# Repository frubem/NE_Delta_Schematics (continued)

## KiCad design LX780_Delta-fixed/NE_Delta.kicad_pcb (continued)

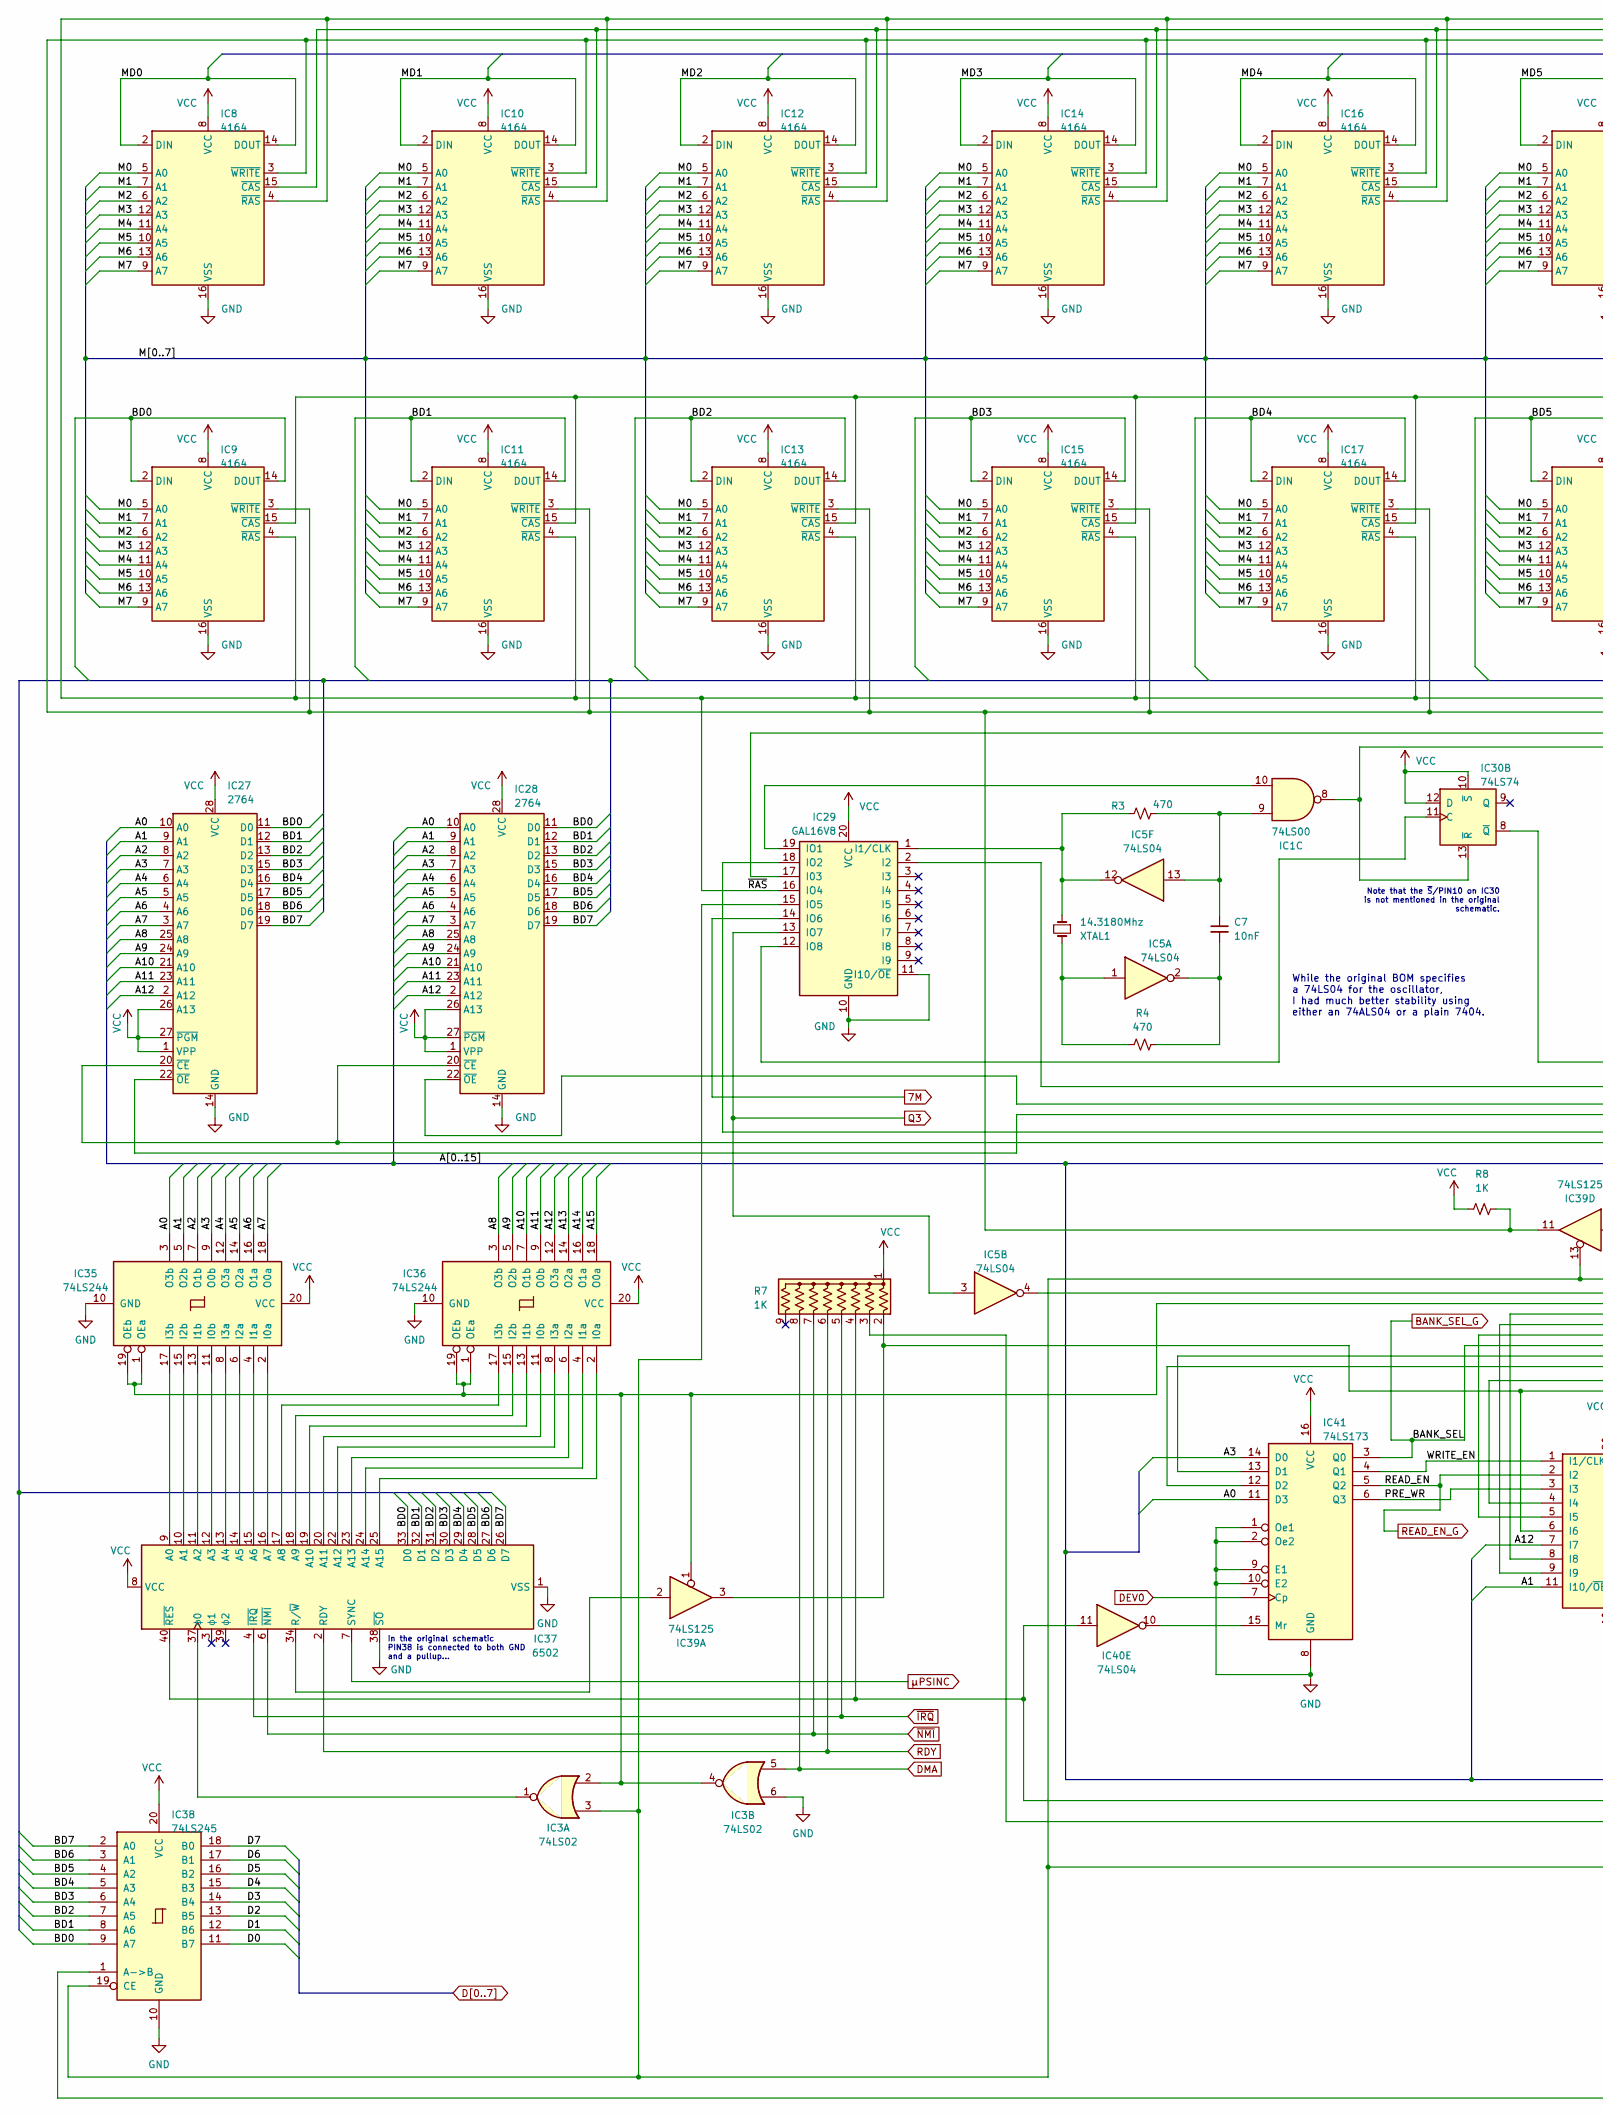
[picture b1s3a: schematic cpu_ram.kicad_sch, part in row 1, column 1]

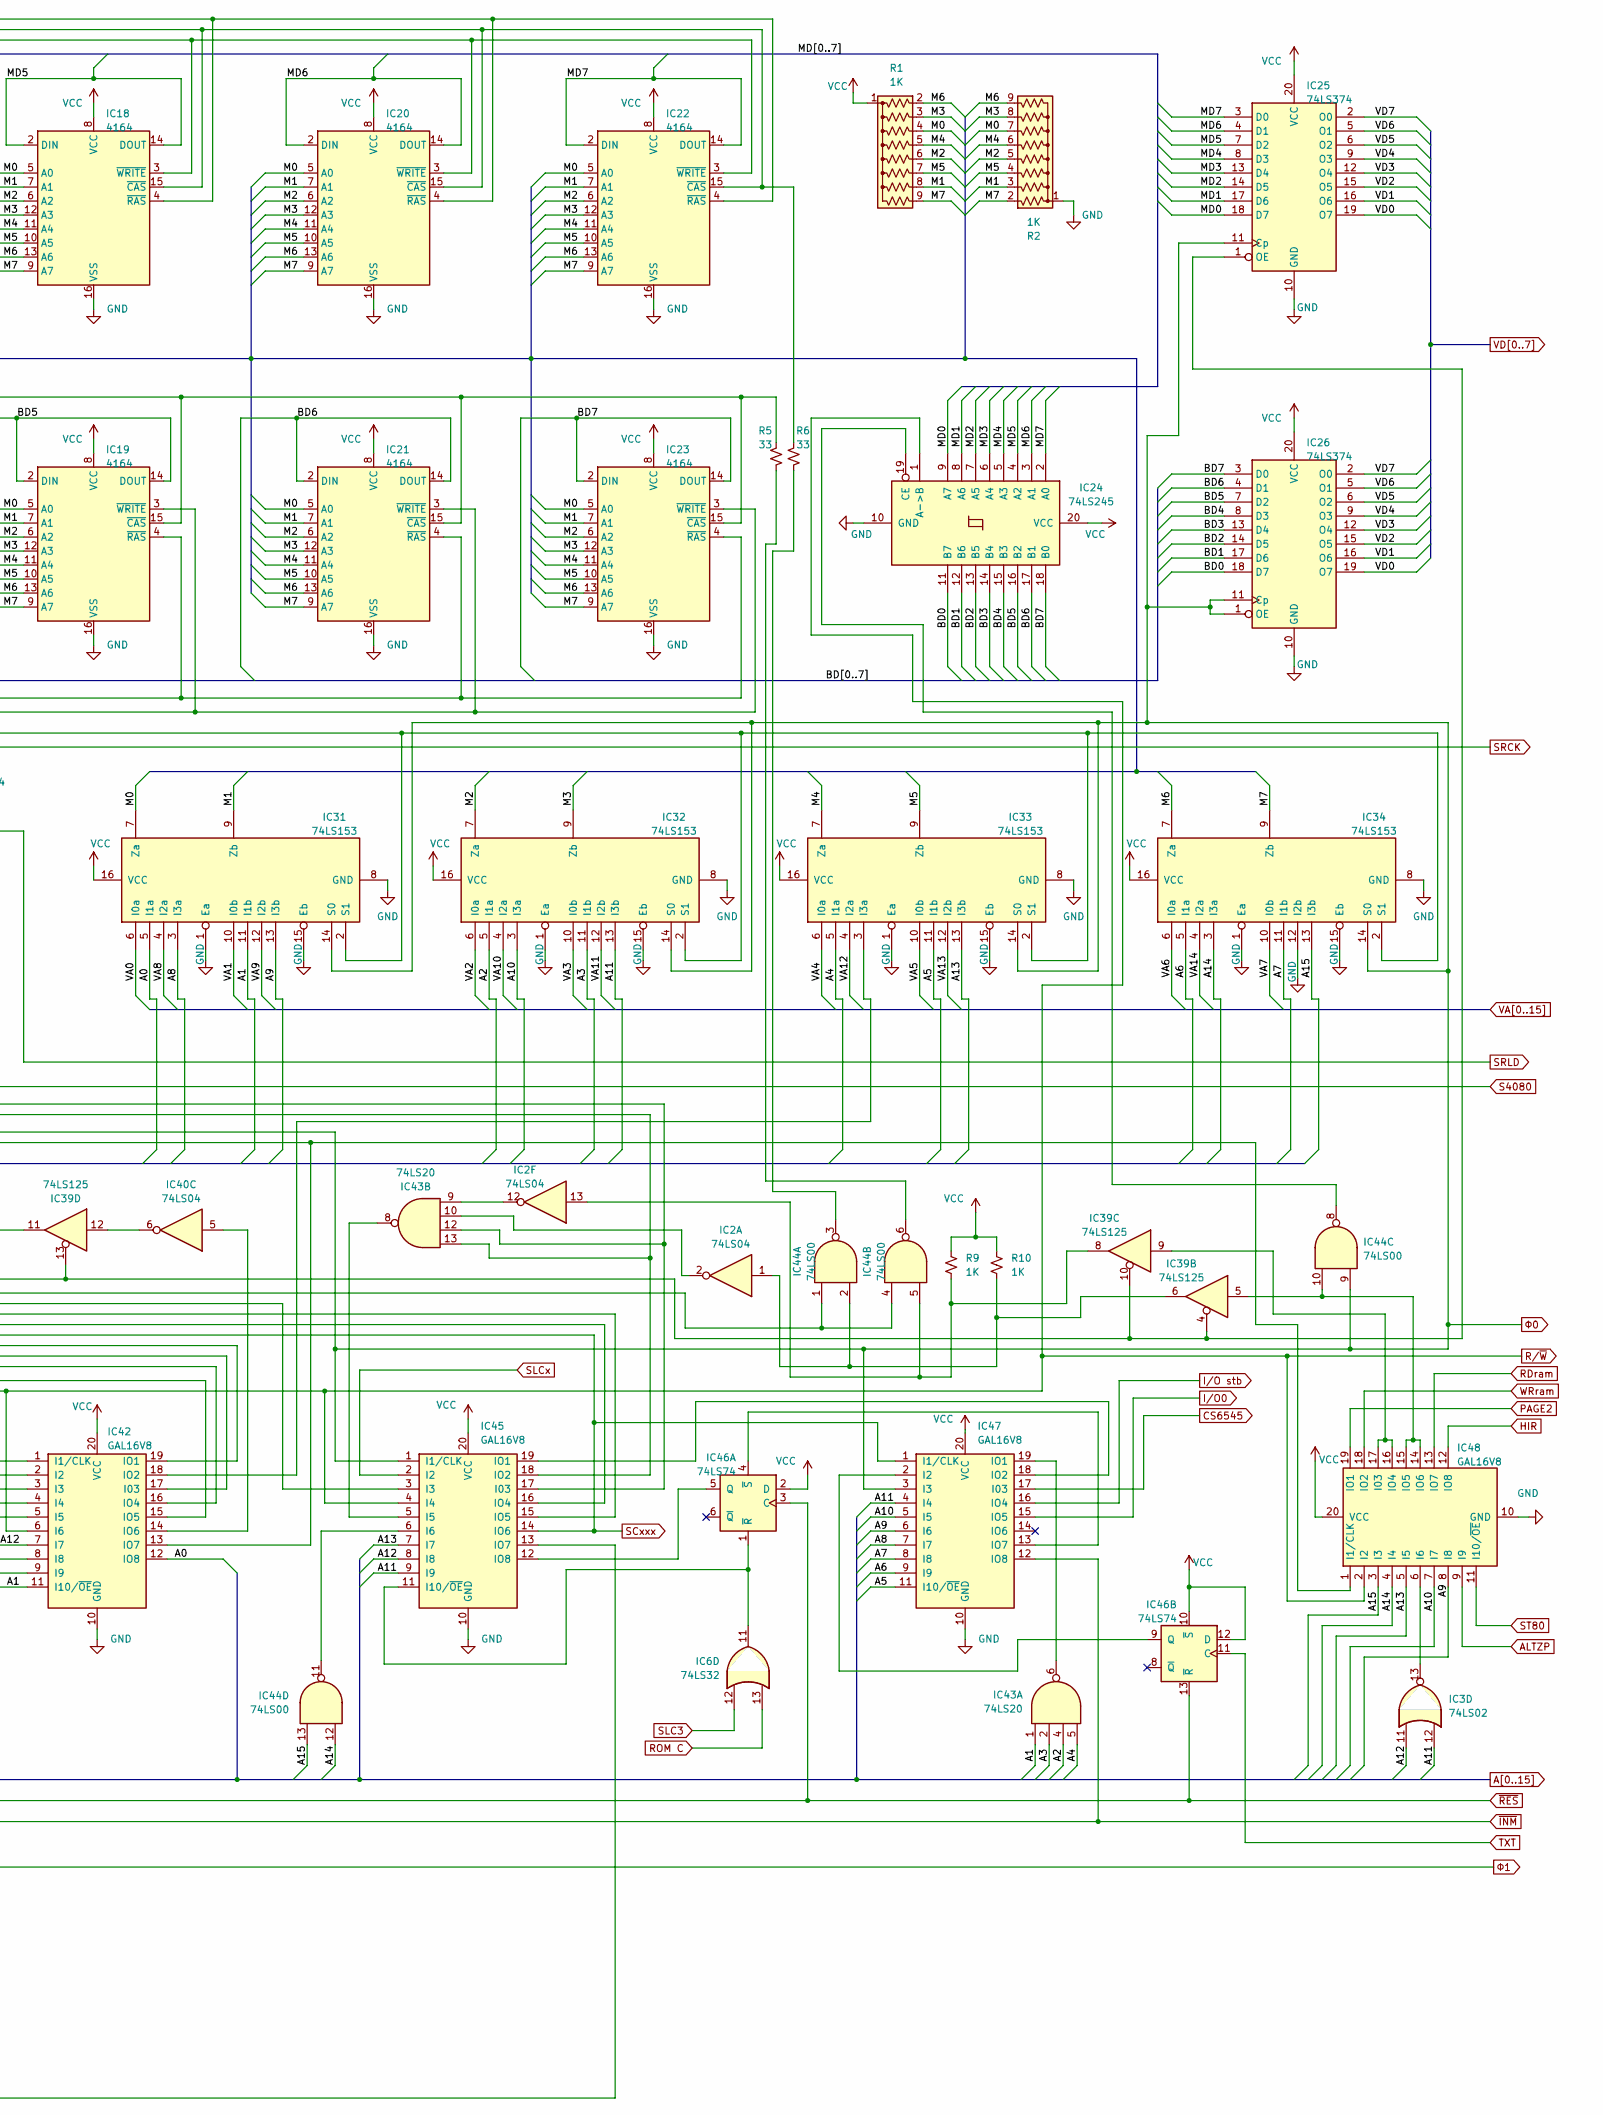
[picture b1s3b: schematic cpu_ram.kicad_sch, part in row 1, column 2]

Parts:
C7: 10nF; C_Disc_D6.0mm_W2.5mm_P5.00mm
IC1, IC44: 74LS00; DIP-14_W7.62mm
IC2, IC5, IC40: 74LS04; DIP-14_W7.62mm
IC3: 74LS02; DIP-14_W7.62mm
IC6: 74LS32; DIP-14_W7.62mm
IC8, IC9, IC10, IC11, IC12, IC13, IC14, IC15, IC16, IC17, IC18, IC19, IC20, IC21, IC22, IC23: 4164; DIP-16_W7.62mm
IC24, IC38: 74LS245; DIP-20_W7.62mm
IC25, IC26: 74LS374; DIP-20_W7.62mm
IC27, IC28: 2764; DIP-28_W15.24mm
IC29, IC42, IC45, IC47, IC48: GAL16V8; DIP-20_W7.62mm
IC30, IC46: 74LS74; DIP-14_W7.62mm
IC31, IC32, IC33, IC34: 74LS153; DIP-16_W7.62mm
IC35, IC36: 74LS244; DIP-20_W7.62mm
IC37: 6502; DIP-40_W15.24mm
IC39: 74LS125; DIP-14_W7.62mm
IC41: 74LS173; DIP-16_W7.62mm
IC43: 74LS20; DIP-14_W7.62mm
R1, R2, R7: 1K; R_Array_SIP9
R3, R4: 470; R_Axial_DIN0309_L9.0mm_D3.2mm_P15.24mm_Horizontal
R5, R6: 33; R_Axial_DIN0309_L9.0mm_D3.2mm_P17.34mm_Horizontal
R8, R9, R10: 1K; R_Axial_DIN0309_L9.0mm_D3.2mm_P15.24mm_Horizontal
XTAL1: 14.3180Mhz; Crystal_HC18-U_Horizontal

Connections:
7M: IC29.14 (IO6); also elsewhere on the board
+5V: IC8.8 (VCC), IC9.8 (VCC), IC10.8 (VCC), IC11.8 (VCC), IC12.8 (VCC), IC13.8 (VCC), IC14.8 (VCC), IC15.8 (VCC), IC16.8 (VCC), IC17.8 (VCC), IC18.8 (VCC), IC19.8 (VCC), IC20.8 (VCC), IC21.8 (VCC), IC22.8 (VCC), IC23.8 (VCC), IC24.20 (VCC), IC25.20 (VCC), IC26.20 (VCC), IC27.1 (VPP), IC27.26 (A13), IC27.27 (~PGM), IC27.28 (VCC), IC28.1 (VPP), IC28.26 (A13), IC28.27 (~PGM), IC28.28 (VCC), IC29.20 (VCC), IC30.10 (~S), IC30.12 (D), IC31.16 (VCC), IC32.16 (VCC), IC33.16 (VCC), IC34.16 (VCC), IC35.20 (VCC), IC36.20 (VCC), IC37.8 (VCC), IC38.20 (VCC), IC41.16 (VCC), IC42.20 (VCC), IC45.20 (VCC), IC46.2 (D), IC46.10 (~S), IC46.12 (D), IC47.20 (VCC), IC48.20 (VCC), R1.1 (common), R7.1 (common), R8.1, R9.1, R10.1; also elsewhere on the board
/CPU and RAM/BD0: IC9.2 (DIN), IC9.14 (DOUT), IC24.11 (B7), IC26.18 (D7), IC27.11 (D0), IC28.11 (D0), IC37.33 (D0), IC38.9 (A7)
/CPU and RAM/BD1: IC11.2 (DIN), IC11.14 (DOUT), IC24.12 (B6), IC26.17 (D6), IC27.12 (D1), IC28.12 (D1), IC37.32 (D1), IC38.8 (A6)
/CPU and RAM/BD2: IC13.2 (DIN), IC13.14 (DOUT), IC24.13 (B5), IC26.14 (D5), IC27.13 (D2), IC28.13 (D2), IC37.31 (D2), IC38.7 (A5)
/CPU and RAM/BD3: IC15.2 (DIN), IC15.14 (DOUT), IC24.14 (B4), IC26.13 (D4), IC27.15 (D3), IC28.15 (D3), IC37.30 (D3), IC38.6 (A4)
/CPU and RAM/BD4: IC17.2 (DIN), IC17.14 (DOUT), IC24.15 (B3), IC26.8 (D3), IC27.16 (D4), IC28.16 (D4), IC37.29 (D4), IC38.5 (A3)
/CPU and RAM/BD5: IC19.2 (DIN), IC19.14 (DOUT), IC24.16 (B2), IC26.7 (D2), IC27.17 (D5), IC28.17 (D5), IC37.28 (D5), IC38.4 (A2)
/CPU and RAM/BD6: IC21.2 (DIN), IC21.14 (DOUT), IC24.17 (B1), IC26.4 (D1), IC27.18 (D6), IC28.18 (D6), IC37.27 (D6), IC38.3 (A1)
/CPU and RAM/BD7: IC23.2 (DIN), IC23.14 (DOUT), IC24.18 (B0), IC26.3 (D0), IC27.19 (D7), IC28.19 (D7), IC37.26 (D7), IC38.2 (A0)
/CPU and RAM/M0: IC8.5 (A0), IC9.5 (A0), IC10.5 (A0), IC11.5 (A0), IC12.5 (A0), IC13.5 (A0), IC14.5 (A0), IC15.5 (A0), IC16.5 (A0), IC17.5 (A0), IC18.5 (A0), IC19.5 (A0), IC20.5 (A0), IC21.5 (A0), IC22.5 (A0), IC23.5 (A0), IC31.7 (Za), R1.4 (R3), R2.7 (R6)
/CPU and RAM/M1: IC8.7 (A1), IC9.7 (A1), IC10.7 (A1), IC11.7 (A1), IC12.7 (A1), IC13.7 (A1), IC14.7 (A1), IC15.7 (A1), IC16.7 (A1), IC17.7 (A1), IC18.7 (A1), IC19.7 (A1), IC20.7 (A1), IC21.7 (A1), IC22.7 (A1), IC23.7 (A1), IC31.9 (Zb), R1.8 (R7), R2.3 (R2)
/CPU and RAM/M2: IC8.6 (A2), IC9.6 (A2), IC10.6 (A2), IC11.6 (A2), IC12.6 (A2), IC13.6 (A2), IC14.6 (A2), IC15.6 (A2), IC16.6 (A2), IC17.6 (A2), IC18.6 (A2), IC19.6 (A2), IC20.6 (A2), IC21.6 (A2), IC22.6 (A2), IC23.6 (A2), IC32.7 (Za), R1.6 (R5), R2.5 (R4)
/CPU and RAM/M3: IC8.12 (A3), IC9.12 (A3), IC10.12 (A3), IC11.12 (A3), IC12.12 (A3), IC13.12 (A3), IC14.12 (A3), IC15.12 (A3), IC16.12 (A3), IC17.12 (A3), IC18.12 (A3), IC19.12 (A3), IC20.12 (A3), IC21.12 (A3), IC22.12 (A3), IC23.12 (A3), IC32.9 (Zb), R1.3 (R2), R2.8 (R7)
/CPU and RAM/M4: IC8.11 (A4), IC9.11 (A4), IC10.11 (A4), IC11.11 (A4), IC12.11 (A4), IC13.11 (A4), IC14.11 (A4), IC15.11 (A4), IC16.11 (A4), IC17.11 (A4), IC18.11 (A4), IC19.11 (A4), IC20.11 (A4), IC21.11 (A4), IC22.11 (A4), IC23.11 (A4), IC33.7 (Za), R1.5 (R4), R2.6 (R5)
/CPU and RAM/M5: IC8.10 (A5), IC9.10 (A5), IC10.10 (A5), IC11.10 (A5), IC12.10 (A5), IC13.10 (A5), IC14.10 (A5), IC15.10 (A5), IC16.10 (A5), IC17.10 (A5), IC18.10 (A5), IC19.10 (A5), IC20.10 (A5), IC21.10 (A5), IC22.10 (A5), IC23.10 (A5), IC33.9 (Zb), R1.7 (R6), R2.4 (R3)
/CPU and RAM/M6: IC8.13 (A6), IC9.13 (A6), IC10.13 (A6), IC11.13 (A6), IC12.13 (A6), IC13.13 (A6), IC14.13 (A6), IC15.13 (A6), IC16.13 (A6), IC17.13 (A6), IC18.13 (A6), IC19.13 (A6), IC20.13 (A6), IC21.13 (A6), IC22.13 (A6), IC23.13 (A6), IC34.7 (Za), R1.2 (R1), R2.9 (R8)
/CPU and RAM/M7: IC8.9 (A7), IC9.9 (A7), IC10.9 (A7), IC11.9 (A7), IC12.9 (A7), IC13.9 (A7), IC14.9 (A7), IC15.9 (A7), IC16.9 (A7), IC17.9 (A7), IC18.9 (A7), IC19.9 (A7), IC20.9 (A7), IC21.9 (A7), IC22.9 (A7), IC23.9 (A7), IC34.9 (Zb), R1.9 (R8), R2.2 (R1)
/CPU and RAM/MD0: IC8.2 (DIN), IC8.14 (DOUT), IC24.9 (A7), IC25.18 (D7)
/CPU and RAM/MD1: IC10.2 (DIN), IC10.14 (DOUT), IC24.8 (A6), IC25.17 (D6)
/CPU and RAM/MD2: IC12.2 (DIN), IC12.14 (DOUT), IC24.7 (A5), IC25.14 (D5)
/CPU and RAM/MD3: IC14.2 (DIN), IC14.14 (DOUT), IC24.6 (A4), IC25.13 (D4)
/CPU and RAM/MD4: IC16.2 (DIN), IC16.14 (DOUT), IC24.5 (A3), IC25.8 (D3)
/CPU and RAM/MD5: IC18.2 (DIN), IC18.14 (DOUT), IC24.4 (A2), IC25.7 (D2)
/CPU and RAM/MD6: IC20.2 (DIN), IC20.14 (DOUT), IC24.3 (A1), IC25.4 (D1)
/CPU and RAM/MD7: IC22.2 (DIN), IC22.14 (DOUT), IC24.2 (A0), IC25.3 (D0)
/CPU and RAM/~RAS: IC8.4 (~RAS), IC9.4 (~RAS), IC10.4 (~RAS), IC11.4 (~RAS), IC12.4 (~RAS), IC13.4 (~RAS), IC14.4 (~RAS), IC15.4 (~RAS), IC16.4 (~RAS), IC17.4 (~RAS), IC18.4 (~RAS), IC19.4 (~RAS), IC20.4 (~RAS), IC21.4 (~RAS), IC22.4 (~RAS), IC23.4 (~RAS), IC29.16 (IO4)
A0: IC27.10 (A0), IC28.10 (A0), IC31.5 (I1a), IC35.3 (O3b), IC41.11 (D3), IC42.12 (IO8); also elsewhere on the board
A1: IC27.9 (A1), IC28.9 (A1), IC31.11 (I1b), IC35.5 (O2b), IC42.11 (I10/~OE), IC43.1; also elsewhere on the board
A2: IC27.8 (A2), IC28.8 (A2), IC32.5 (I1a), IC35.7 (O1b), IC43.4; also elsewhere on the board
A3: IC27.7 (A3), IC28.7 (A3), IC32.11 (I1b), IC35.9 (O0b), IC41.14 (D0), IC43.2; also elsewhere on the board
A4: IC27.6 (A4), IC28.6 (A4), IC33.5 (I1a), IC35.12 (O3a), IC43.5; also elsewhere on the board
A5: IC27.5 (A5), IC28.5 (A5), IC33.11 (I1b), IC35.14 (O2a), IC47.11 (I10/~OE); also elsewhere on the board
A6: IC27.4 (A6), IC28.4 (A6), IC34.5 (I1a), IC35.16 (O1a), IC47.9 (I9); also elsewhere on the board
A7: IC27.3 (A7), IC28.3 (A7), IC34.11 (I1b), IC35.18 (O0a), IC47.8 (I8); also elsewhere on the board
A8: IC27.25 (A8), IC28.25 (A8), IC31.3 (I3a), IC36.3 (O3b), IC47.7 (I7); also elsewhere on the board
A9: IC27.24 (A9), IC28.24 (A9), IC31.13 (I3b), IC36.5 (O2b), IC47.6 (I6), IC48.8 (I8); also elsewhere on the board
A10: IC27.21 (A10), IC28.21 (A10), IC32.3 (I3a), IC36.7 (O1b), IC47.5 (I5), IC48.7 (I7); also elsewhere on the board
A11: IC3.12, IC27.23 (A11), IC28.23 (A11), IC32.13 (I3b), IC36.9 (O0b), IC45.9 (I9), IC47.4 (I4); also elsewhere on the board
A12: IC3.11, IC27.2 (A12), IC28.2 (A12), IC36.12 (O3a), IC42.7 (I7), IC45.8 (I8); also elsewhere on the board
A13: IC33.13 (I3b), IC36.14 (O2a), IC45.7 (I7), IC48.5 (I5); also elsewhere on the board
A14: IC34.3 (I3a), IC36.16 (O1a), IC44.12, IC48.4 (I4); also elsewhere on the board
A15: IC34.13 (I3b), IC36.18 (O0a), IC44.13, IC48.3 (I3); also elsewhere on the board
ALTZP: IC48.9 (I9); also elsewhere on the board
CS6545: IC47.17 (I03); also elsewhere on the board
D0: IC38.11 (B7); also elsewhere on the board
D1: IC38.12 (B6); also elsewhere on the board
D2: IC38.13 (B5); also elsewhere on the board
D3: IC38.14 (B4); also elsewhere on the board
D4: IC38.15 (B3); also elsewhere on the board
D5: IC38.16 (B2); also elsewhere on the board
D6: IC38.17 (B1); also elsewhere on the board
D7: IC38.18 (B0); also elsewhere on the board
DEV0: IC41.7 (Cp); also elsewhere on the board
DMA: IC3.5, R7.8 (R7); also elsewhere on the board
GND: IC3.6, IC8.16 (VSS), IC9.16 (VSS), IC10.16 (VSS), IC11.16 (VSS), IC12.16 (VSS), IC13.16 (VSS), IC14.16 (VSS), IC15.16 (VSS), IC16.16 (VSS), IC17.16 (VSS), IC18.16 (VSS), IC19.16 (VSS), IC20.16 (VSS), IC21.16 (VSS), IC22.16 (VSS), IC23.16 (VSS), IC24.10 (GND), IC25.10 (GND), IC26.10 (GND), IC27.14 (GND), IC28.14 (GND), IC29.10 (GND), IC29.11 (I10/~OE), IC31.1 (Ea), IC31.8 (GND), IC31.15 (Eb), IC32.1 (Ea), IC32.8 (GND), IC32.15 (Eb), IC33.1 (Ea), IC33.8 (GND), IC33.15 (Eb), IC34.1 (Ea), IC34.8 (GND), IC34.12 (I2b), IC34.15 (Eb), IC35.10 (GND), IC36.10 (GND), IC37.1 (VSS), IC37.21 (VSS), IC37.38 (~SO), IC38.10 (GND), IC41.1 (Oe1), IC41.2 (Oe2), IC41.8 (GND), IC41.9 (E1), IC41.10 (E2), IC42.10 (GND), IC45.10 (GND), IC47.10 (GND), IC48.10 (GND), R2.1 (common); also elsewhere on the board
HIR: IC48.12 (IO8); also elsewhere on the board
I/O0: IC47.15 (IO5); also elsewhere on the board
I/O stb: IC47.16 (IO4); also elsewhere on the board
unnamed: C7.1, IC1.9, IC5.13, R3.2
unnamed: C7.2, IC5.2, R4.2
unnamed: IC2.1, IC39.6, IC44.2, R10.2
unnamed: IC2.2, IC43.10
unnamed: IC2.12, IC43.9
unnamed: IC2.13, IC39.8, IC44.5, R9.2
unnamed: IC5.1, R4.1, XTAL1.2
unnamed: IC8.15 (~CAS), IC10.15 (~CAS), IC12.15 (~CAS), IC14.15 (~CAS), IC16.15 (~CAS), IC18.15 (~CAS), IC20.15 (~CAS), IC22.15 (~CAS), R6.1
unnamed: IC8.3 (~WRITE), IC9.3 (~WRITE), IC10.3 (~WRITE), IC11.3 (~WRITE), IC12.3 (~WRITE), IC13.3 (~WRITE), IC14.3 (~WRITE), IC15.3 (~WRITE), IC16.3 (~WRITE), IC17.3 (~WRITE), IC18.3 (~WRITE), IC19.3 (~WRITE), IC20.3 (~WRITE), IC21.3 (~WRITE), IC22.3 (~WRITE), IC23.3 (~WRITE), IC39.11, R8.2
unnamed: IC9.15 (~CAS), IC11.15 (~CAS), IC13.15 (~CAS), IC15.15 (~CAS), IC17.15 (~CAS), IC19.15 (~CAS), IC21.15 (~CAS), IC23.15 (~CAS), R5.1
unnamed: IC24.19 (CE), IC44.8
unnamed: IC27.20 (~CE), IC28.20 (~CE), IC42.13 (IO7), IC48.1 (I1/CLK)
unnamed: IC27.22 (~OE), IC43.13, IC45.18 (IO2)
unnamed: IC28.22 (~OE), IC43.12, IC45.17 (I03)
unnamed: IC5.12, IC29.1 (I1/CLK), R3.1, XTAL1.1
unnamed: IC29.17 (I03), IC31.2 (S1), IC32.2 (S1), IC33.2 (S1), IC34.2 (S1)
unnamed: IC1.10, IC29.19 (IO1)
unnamed: IC29.12 (IO8), IC30.11 (C)
unnamed: IC33.3 (I3a), IC42.18 (IO2)
unnamed: IC35.2 (I0a), IC37.16 (A7)
unnamed: IC35.11 (I0b), IC37.12 (A3)
unnamed: IC35.4 (I1a), IC37.15 (A6)
unnamed: IC35.13 (I1b), IC37.11 (A2)
unnamed: IC35.6 (I2a), IC37.14 (A5)
unnamed: IC35.15 (I2b), IC37.10 (A1)
unnamed: IC35.8 (I3a), IC37.13 (A4)
unnamed: IC35.17 (I3b), IC37.9 (A0)
unnamed: IC3.2, IC3.4, IC35.1 (OEa), IC35.19 (OEb), IC36.1 (OEa), IC36.19 (OEb), IC39.1, IC45.3 (I3)
unnamed: IC36.2 (I0a), IC37.25 (A15)
unnamed: IC36.11 (I0b), IC37.20 (A11)
unnamed: IC36.4 (I1a), IC37.24 (A14)
unnamed: IC36.13 (I1b), IC37.19 (A10)
unnamed: IC36.6 (I2a), IC37.23 (A13)
unnamed: IC36.15 (I2b), IC37.18 (A9)
unnamed: IC36.8 (I3a), IC37.22 (A12)
unnamed: IC36.17 (I3b), IC37.17 (A8)
unnamed: IC37.34 (R/~W), IC39.2
unnamed: IC3.1, IC37.37 (ϕ0)
unnamed: IC38.1 (A->B), IC45.13 (IO7)
unnamed: IC39.12, IC40.6
unnamed: IC41.13 (D1), IC42.17 (I03)
unnamed: IC41.12 (D2), IC42.16 (IO4)
unnamed: IC40.10, IC41.15 (Mr)
unnamed: IC41.4 (Q1), IC42.1 (I1/CLK)
unnamed: IC41.6 (Q3), IC42.3 (I3)
unnamed: IC42.4 (I4), IC42.15 (IO5)
unnamed: IC42.8 (I8), IC45.15 (IO5)
unnamed: IC42.9 (I9), IC45.16 (IO4)
unnamed: IC40.5, IC42.14 (IO6)
unnamed: IC5.4, IC44.1, IC44.4
unnamed: IC44.3, R6.2
unnamed: IC44.6, R5.2
unnamed: IC43.8, IC45.5 (I5)
unnamed: IC44.11, IC45.6 (I6)
unnamed: IC6.11, IC45.11 (I10/~OE), IC46.1 (~R)
unnamed: IC45.19 (IO1), IC47.18 (IO2)
unnamed: IC45.12 (IO8), IC46.5 (Q)
unnamed: IC46.4 (~S), IC47.13 (IO7)
unnamed: IC46.9 (Q), IC47.2 (I2)
unnamed: IC43.6, IC47.19 (IO1)
unnamed: IC39.9, IC48.16 (IO4), IC48.17 (I03)
unnamed: IC3.13, IC48.6 (I6)
unnamed: IC39.5, IC44.10, IC48.14 (IO6), IC48.15 (IO5)
PAGE2: IC48.19 (IO1); also elsewhere on the board
Q3: IC5.3, IC29.13 (IO7); also elsewhere on the board
RDY: IC37.2 (RDY), R7.6 (R5); also elsewhere on the board
RDram: IC48.13 (IO7); also elsewhere on the board
ROM C: IC6.13; also elsewhere on the board
R/~W: IC24.1 (A->B), IC39.3, IC42.6 (I6), IC45.4 (I4), IC48.2 (I2), R7.2 (R1); also elsewhere on the board
S4080: IC29.2 (I2); also elsewhere on the board
SCxxx: IC42.5 (I5), IC45.14 (IO6), IC47.1 (I1/CLK); also elsewhere on the board
SLC3: IC6.12; also elsewhere on the board
SLCx: IC45.2 (I2); also elsewhere on the board
SRCK: IC1.8, IC30.13 (~R); also elsewhere on the board
SRLD: IC30.8 (~Q); also elsewhere on the board
ST80: IC48.11 (I10/~OE); also elsewhere on the board
TXT: IC46.11 (C); also elsewhere on the board
VA0: IC31.6 (I0a); also elsewhere on the board
VA1: IC31.10 (I0b); also elsewhere on the board
VA2: IC32.6 (I0a); also elsewhere on the board
VA3: IC32.10 (I0b); also elsewhere on the board
VA4: IC33.6 (I0a); also elsewhere on the board
VA5: IC33.10 (I0b); also elsewhere on the board
VA6: IC34.6 (I0a); also elsewhere on the board
VA7: IC34.10 (I0b); also elsewhere on the board
VA8: IC31.4 (I2a); also elsewhere on the board
VA9: IC31.12 (I2b); also elsewhere on the board
VA10: IC32.4 (I2a); also elsewhere on the board
VA11: IC32.12 (I2b); also elsewhere on the board
VA12: IC33.4 (I2a); also elsewhere on the board
VA13: IC33.12 (I2b); also elsewhere on the board
VA14: IC34.4 (I2a); also elsewhere on the board
VD0: IC25.19 (O7), IC26.19 (O7); also elsewhere on the board
VD1: IC25.16 (O6), IC26.16 (O6); also elsewhere on the board
VD2: IC25.15 (O5), IC26.15 (O5); also elsewhere on the board
VD3: IC25.12 (O4), IC26.12 (O4); also elsewhere on the board
VD4: IC25.9 (O3), IC26.9 (O3); also elsewhere on the board
VD5: IC25.6 (O2), IC26.6 (O2); also elsewhere on the board
VD6: IC25.5 (O1), IC26.5 (O1); also elsewhere on the board
VD7: IC25.2 (O0), IC26.2 (O0); also elsewhere on the board
WRram: IC48.18 (IO2); also elsewhere on the board
~INM: IC47.12 (IO8), R7.3 (R2); also elsewhere on the board
~IRQ: IC37.4 (~IRQ), R7.5 (R4); also elsewhere on the board
~NMI: IC37.6 (~NMI), R7.7 (R6); also elsewhere on the board
~RES: IC37.40 (~RES), IC40.11, IC46.3 (C), IC46.13 (~R), R7.4 (R3); also elsewhere on the board
Φ0: IC25.11 (Cp), IC26.1 (OE), IC26.11 (Cp), IC29.18 (IO2), IC31.14 (S0), IC32.14 (S0), IC33.14 (S0), IC34.14 (S0), IC44.9, IC45.1 (I1/CLK), IC47.3 (I3); also elsewhere on the board
Φ1: IC3.3, IC25.1 (OE), IC29.15 (IO5), IC38.19 (CE), IC39.4, IC39.10, IC39.13; also elsewhere on the board
μPSINC: IC37.7 (SYNC); also elsewhere on the board

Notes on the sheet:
In the original schematic PIN38 is connected to both GND and a pullup...
While the original BOM specifies a 74LS04 for the oscillator, I had much better stability using either an 74ALS04 or a plain 7404.
Note that the ~{S}/PIN10 on IC30 is not mentioned in the original schematic.
